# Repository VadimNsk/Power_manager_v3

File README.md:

# Power_manager_v3
Модуль управления питанием двух нагрузок

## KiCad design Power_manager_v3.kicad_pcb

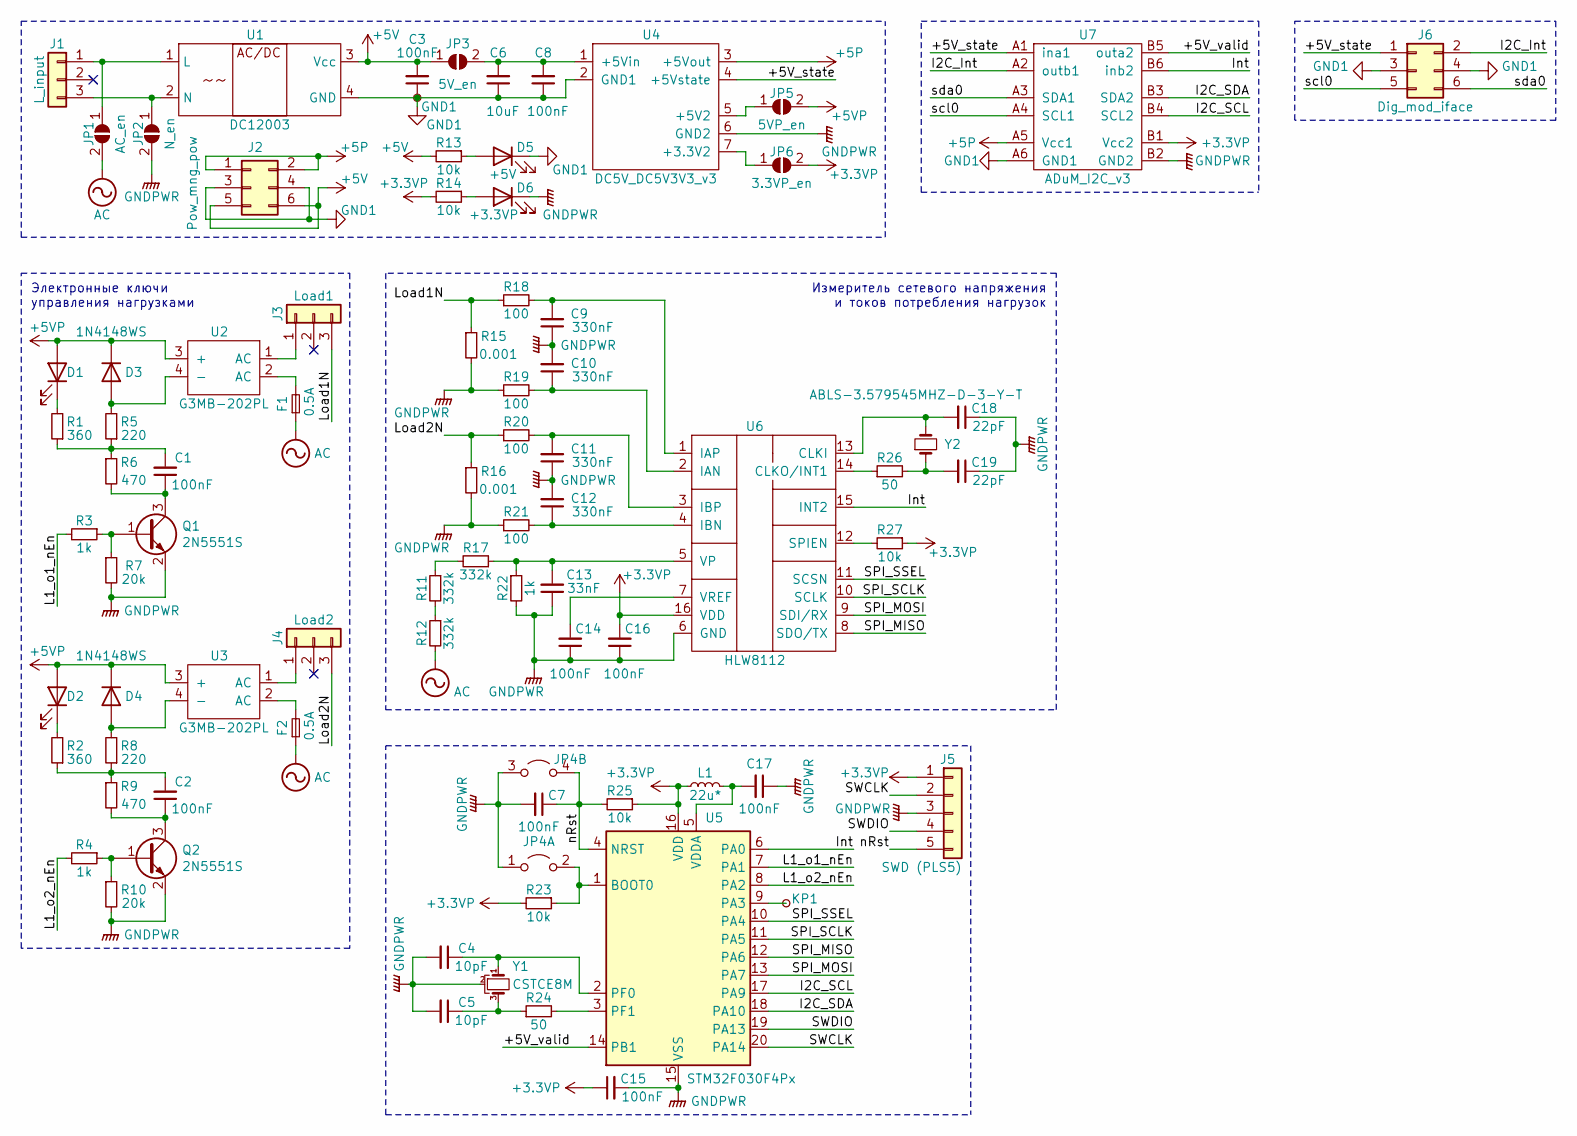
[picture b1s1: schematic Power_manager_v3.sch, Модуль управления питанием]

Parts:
C1, C2, C3, C7, C8, C14, C15, C16, C17: 100nF; C_0603_1608Metric
C4, C5: 10pF; C_0603_1608Metric
C6: 10uF; C_0603_1608Metric
C9, C10, C11, C12: 330nF; C_0805_2012Metric; Part Number GRM219R71H334KA88D
C13: 33nF; C_0805_2012Metric; Part Number GRM219R71H333KA01D
C18, C19: 22pF; C_0603_1608Metric
D1, D2: LED; LED_0603_1608Metric
D3, D4: 1N4148WS; D_SOD-323
D5: +5V; LED_0603_1608Metric
D6: +3.3VP; LED_0603_1608Metric
F1, F2: 0.5A; R_Axial_DIN0207_L6.3mm_D2.5mm_P7.62mm_Horizontal
GND1: TestPoint_Small; TestPoint_THTPad_D2.0mm_Drill1.0mm
J1: L_input; PinHeader_1x03_P2.54mm_Vertical_for_DG301-5.0-02P
J2: Pow_mng_pow; PinSocket_2x03_P1.27mm_Horizontal
J3: Load1; PinHeader_1x03_P2.54mm_Vertical_for_DG301-5.0-02P
J4: Load2; PinHeader_1x03_P2.54mm_Vertical_for_DG301-5.0-02P
J5: SWD (PLS5); PinSocket_1x05_P1.27mm_Vertical_SMD_Pin1Right
J6: Dig_mod_iface; PinSocket_2x03_P1.27mm_Horizontal
JP1: AC_en; SolderJumper-2_P1.3mm_Open_TrianglePad1.0x1.5mm
JP2: N_en; SolderJumper-2_P1.3mm_Open_TrianglePad1.0x1.5mm
JP3: 5V_en; SolderJumper-2_P1.3mm_Open_TrianglePad1.0x1.5mm
JP4: Jumper_2x2_Open; PinHeader_2x02_P1.27mm_Vertical
JP5: 5VP_en; SolderJumper-2_P1.3mm_Open_TrianglePad1.0x1.5mm
JP6: 3.3VP_en; SolderJumper-2_P1.3mm_Open_TrianglePad1.0x1.5mm
KP1: TestPoint_Small; TestPoint_THTPad_D1.5mm_Drill0.7mm
L1: 22u*; R_0805_2012Metric
Q1, Q2: 2N5551S; SOT-23
R1, R2: 360; R_0603_1608Metric
R3, R4: 1k; R_0603_1608Metric
R5, R8: 220; R_0603_1608Metric
R6, R9: 470; R_0603_1608Metric
R7, R10: 20k; R_0603_1608Metric
R11, R12, R17: 332k; R_0805_2012Metric; Part Number RI0805L3323FT
R13, R14, R23, R25, R27: 10k; R_0603_1608Metric
R15, R16: 0.001; R_MiniMELF_MMA-0204; Part Number WSHM28181L000FEA
R18, R19, R20, R21: 100; R_0805_2012Metric; Part Number CRS0805-FX-1000ELF
R22: 1k; R_0805_2012Metric; Part Number CRS0805-FX-1001ELF
R24, R26: 50; R_0603_1608Metric
U1: DC12003
U2, U3: G3MB-202PL
U4: DC5V_DC5V3V3_v3
U5: STM32F030F4Px; TSSOP-20_4.4x6.5mm_P0.65mm
U6: HLW8112; SSOP-16_4.4x5.2mm_P0.65mm
U7: ADuM_I2C_v3; ADuM_I2C_Horizontal
Y1: CSTCE8M; Resonator_SMD_muRata_CSTxExxV-3Pin_3.0x1.1mm_HandSoldering
Y2: ABLS-3.579545MHZ-D-3-Y-T; Resonator_SMD_muRata_CSTxExxV-3Pin_3.0x1.1mm_HandSoldering

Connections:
+3.3VP: C15.1, C16.2, J5.1, JP6.2 (B), L1.1, R14.2, R23.2, R25.1, R27.1, U5.16 (VDD), U6.16 (VDD), U7.B1 (Vcc2)
+5P: J2.1, J2.2, U4.3 (+5Vout), U7.A5 (Vcc1)
+5V: C3.2, J2.5, J2.6, JP3.1 (A), R13.2, U1.3 (Vcc)
+5VP: D1.2 (A), D2.2 (A), D3.1 (K), D4.1 (K), JP5.2 (B), U2.3 (+), U3.3 (+)
/+5V_state: J6.1, U4.4 (+5Vstate), U7.A1 (ina1)
/+5V_valid: U5.14 (PB1), U7.B5 (outa2)
/I2C_Int: J6.2, U7.A2 (outb1)
/I2C_SCL: U5.17 (PA9), U7.B4 (SCL2)
/I2C_SDA: U5.18 (PA10), U7.B3 (SDA2)
/Int: U5.6 (PA0), U6.15 (INT2), U7.B6 (inb2)
/L1_o1_nEn: R3.2, U5.7 (PA1)
/L1_o2_nEn: R4.2, U5.8 (PA2)
/Load1N: J3.3, R15.1, R18.1
/Load2N: J4.3, R16.1, R20.1
/SPI_MISO: U5.12 (PA6), U6.8 (SDO/TX)
/SPI_MOSI: U5.13 (PA7), U6.9 (SDI/RX)
/SPI_SCLK: U5.11 (PA5), U6.10 (SCLK)
/SPI_SSEL: U5.10 (PA4), U6.11 (SCSN)
/SWCLK: J5.2, U5.20 (PA14)
/SWDIO: J5.4, U5.19 (PA13)
/nRst: C7.1, J5.5, JP4.4 (B), R25.2, U5.4 (NRST)
/scl0: J6.5, U7.A4 (SCL1)
/sda0: J6.6, U7.A3 (SDA1)
AC: F1.1, F2.1, JP1.2 (B), R12.2
GND1: C3.1, C6.1, C8.1, D5.1 (K), GND1.1, J2.3, J2.4, J6.3, J6.4, U1.4 (GND), U4.2 (GND1), U7.A6 (GND1)
GNDPWR: C4.2, C5.2, C7.2, C9.1, C10.2, C11.1, C12.2, C13.1, C14.1, C15.2, C16.1, C17.1, C18.1, C19.1, D6.1 (K), J5.3, JP2.2 (B), JP4.1 (A), JP4.3 (A), Q1.2 (E), Q2.2 (E), R7.2, R10.2, R15.2, R16.2, R19.1, R21.1, R22.2, U4.6 (GND2), U5.15 (VSS), U6.6 (GND), U7.B2 (GND2), Y1.2
unnamed: C1.1, Q1.3 (C), R6.2
unnamed: C1.2, R1.1, R5.1, R6.1
unnamed: C2.1, Q2.3 (C), R9.2
unnamed: C2.2, R2.1, R8.1, R9.1
unnamed: C4.1, U5.2 (PF0), Y1.1
unnamed: C5.1, R24.1, Y1.3
unnamed: C6.2, C8.2, JP3.2 (B), U4.1 (+5Vin)
unnamed: C9.2, R18.2, U6.1 (IAP)
unnamed: C10.1, R19.2, U6.2 (IAN)
unnamed: C11.2, R20.2, U6.3 (IBP)
unnamed: C12.1, R21.2, U6.4 (IBN)
unnamed: C13.2, R17.1, R22.1, U6.5 (VP)
unnamed: C14.2, U6.7 (VREF)
unnamed: C17.2, L1.2, U5.5 (VDDA)
unnamed: C18.2, U6.13 (CLKI), Y2.2
unnamed: C19.2, R26.2, Y2.1
unnamed: D1.1 (K), R1.2
unnamed: D2.1 (K), R2.2
unnamed: D3.2 (A), R5.2, U2.4 (-)
unnamed: D4.2 (A), R8.2, U3.4 (-)
unnamed: D5.2 (A), R13.1
unnamed: D6.2 (A), R14.1
unnamed: F1.2, U2.2 (AC)
unnamed: F2.2, U3.2 (AC)
unnamed: J1.1, JP1.1 (A), U1.1 (L)
unnamed: J1.3, JP2.1 (A), U1.2 (N)
unnamed: J3.1, U2.1 (AC)
unnamed: J4.1, U3.1 (AC)
unnamed: JP4.2 (B), R23.1, U5.1 (BOOT0)
unnamed: JP5.1 (A), U4.5 (+5V2)
unnamed: JP6.1 (A), U4.7 (+3.3V2)
unnamed: KP1.1, U5.9 (PA3)
unnamed: Q1.1 (B), R3.1, R7.1
unnamed: Q2.1 (B), R4.1, R10.1
unnamed: R11.1, R17.2
unnamed: R11.2, R12.1
unnamed: R24.2, U5.3 (PF1)
unnamed: R26.1, U6.14 (CLKO/INT1)
unnamed: R27.2, U6.12 (SPIEN)

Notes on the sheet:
Электронные ключи управления нагрузками
Измеритель сетевого напряжения и токов потребления нагрузок

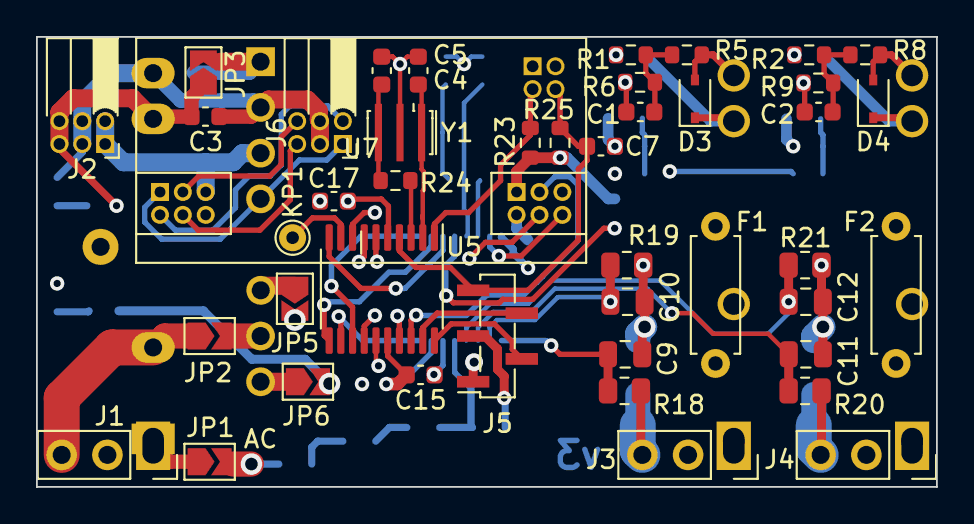
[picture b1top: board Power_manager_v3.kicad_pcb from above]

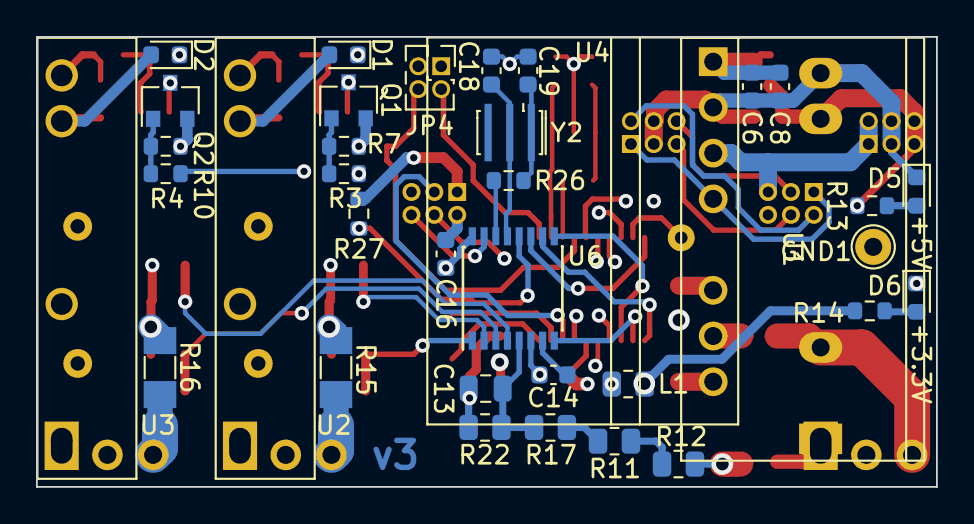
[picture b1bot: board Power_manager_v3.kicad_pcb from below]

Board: 4 copper layers, 50.0 x 25.0 mm, 80 parts (36 on the bottom side), 65 nets.

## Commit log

2021-11-27 Добавлены основные файлы в репозиторий.
2021-12-25 Окончена трассировка печатной платы
2022-01-01 Исправления в схеме и в печатной плате.
2022-01-16 Мелкие исправления в схеме и плате
2022-01-18 Добавлен BOM-файл в HTML-формате, гербера и файлы сверловки
2022-01-18 Сформирован перечень элементов, 3D-модель, исправлены ошибки, реализована панелизация платы.
2022-02-17 Последние изменения в BOM
